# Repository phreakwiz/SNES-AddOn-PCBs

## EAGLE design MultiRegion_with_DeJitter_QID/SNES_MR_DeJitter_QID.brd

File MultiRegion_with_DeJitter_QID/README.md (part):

## Multi-Region Mod for any SNES

**Free your SNES**

(picture shows last prototype PCB installed on a SNS-CPU-RGB-01)

### Acknowledgement and Licensing

This PCB, its idea and design, is a confluence of multiple projects. All credits and rights are going to their respective creators:

- **SuperCIC-lock** by Ikari_01
  Copyright (c) 2010 by Maximilian Rehkopf under GNU GPLv2
  Source: [sd2snes homepage](https://sd2snes.de/blog/cool-stuff/supercic)
- **uIGR** by Ikari_01 and borti4938
  Copyright (c) 2010 by Maximilian Rehkopf under GNU GPLv2,
  and modifications copyright (c) 2015 by Peter Bartmann under GNU GPLv2
  Source: [sd2snes homepage](https://sd2snes.de/blog/cool-stuff/in-game-reset), [GitHub repository](https://github.com/borti4938/Switchless-Mods/tree/master/SNES/uigr_16f684)
- **Region Patch** built in SNES by Ikari_01 (initial idea and detection using SuperCIC-lock) and borti4938 (schematic refinement and CPLD implementation)
  Initial idea (c) 2012 ikari_01, CPLD implementation as used here covered in DeJitter license
  Source: [sd2snes homepage](https://sd2snes.de/files/supercic-213f.pdf)
- **DeJitter** by marqs85
  Copyright (c) 2017-2018 Markus Hiienkari under MIT
  and modifications and additions copyright (c) 2019 Peter Bartmann under MIT
  Source: [Original GitHub Repository](https://github.com/marqs85/snes_dejitter), [Forked GitHub repository](https://github.com/borti4938/snes_dejitter/tree/regionpatch%2Bdejitter)
- **DFO** by micro
  Copyright / created 2015 by Jakob Schäfer without licensing (but given to retro community)
  Source: mirror in [this repository](./dfo), with minor adaptations and with several original sources noted [in the Source.md file](./dfo/SOURCE.md)
- **PCB design** by borti4938
  Copyright (c) 2019 by Peter Bartmann under GNU GPLv3

### Features

- **SuperCIC:** lockout chip replacement 50Hz/60Hz switch cabability
- **uIGR:** controller input sniffing to perform certain actions like reset or 60Hz and 50Hz switch up on certain combinations
- **Region Patch:** overrides region protection based on picture processing status reads
- **DeJitter:** removes jitter on sync for NTSC mode
- **DFO:** dual frequency oscillator, here used to switch between base clocks for 50Hz, 60Hz video-modes

### PCB Description

#### Solder Pads

These are just general descriptions of the in- and outputs. Please refer to the installation instructions for each [specific mainboard version](./installation/) (if exists) for suitable connections.

- **/Rst.o:** (output (2x))
  Low-active reset output. This has to be connected with CIC-lock pad 10 / S-APU pin 100. Connect either pad.
- **Rst.i:** (input)
  High-active reset input. This pad has to be connected with the CIC-lock pad 8 (reset button).
- **LED.Re:** (output)
  LED driver for replacement LED; usually red. Output is active on 60Hz and auto video mode and off on 50Hz (or vice versa if SJ21 is set (common anode LED))
- **LED.Gr:** (output)
  LED driver for replacement LED; usually green. Output is active on 50Hz and auto video mode and off on 60Hz (or vice versa if SJ21 is set (common anode LED))
- **Ctrl.port.10:** (input)
  Input for controller 1 sniffing (data latch signal). _Port_ refers to flat cable connector of the whole controller panel, i.e. pin is equivalent for controller connector pin 3.
- **Ctrl.port.8:** (input)
  Input for controller 1 sniffing (data clock signal). _Port_ refers to flat cable connector of the whole controller panel, i.e. pin is equivalent for controller connector pin 2.
- **Ctrl.port.6:** (input)
  Input for controller 1 sniffing (serial data signal). _Port_ refers to flat cable connector of the whole controller panel, i.e. pin is equivalent for controller connector pin 4.
- **Vmode:** (output)
  Output sets the PPU video mode at S-PPU1 pin 24 and S-PPU2 pin 30 or at the S-CPUN pin 111. Output is active on 50Hz mode and inactive on 60Hz mode.
- **/Vmode:** (output (2x))
  Output sets the video encoding at the video encoder, which is pin 19 of the S-ENC and pin 9 of the S-RGB. Connect just on of the pads!
- **Clk.CIC:** (input)
  Input for the SuperCIC-lock clock, which comes from CIC pad 7.
- **MClk.o:** (output)
  Output for the (de-jittered) master clock of the SNES. This is approx. 21.477MHz in NTSC mode and appr. 17.734MHz (1Chip-SNES, SJ32 not set) or appr. 21.281MHz (non-1Chip, SJ32 set) in PAL mode. Please refer to the general installation note to see whether and how to connect this pad properly.
- **CClk.o:** (output)
  Output of the color carrier, which is appr. 3.380MHz in NTSC mode and appr. 4.433MHz in PAL mode. Please refer to the general installation note to see whether and how to connect this pad properly.
- **/CS.i:** (input (2x since SMR20190813)
  Input of the 'original' (non-de-jittered) composite sync. This comes from pin 100 S-PPU2 or pin 151 S-CPUN.
- **/CS.o buf:** (output)
  Buffered (de-jittered) composite sync output. This is meant to be connected directly to the multiout pin 3. Note: The PAL SNES has 12V connected to this pin, which has to be removed.
- **/CS.o raw:** (output (2x))
  Raw output of the CPLD, which has 3.3V high and 0V low level. Connect it to the video encode, which is pin 8 of the S-ENC or pin 7 of the S-RGB (both chips allows 2.0V for input high, so 3.3V high is sufficient.)

#### Jumper

- **SJ11:** alternative clock for the SuperCIC; close this jumper if you don't connect the _Clk.CIC_ pad in order to use the clock meant for the CIC-key
- **SJ21:** close this jumper if you use a LED with a common anode. Otherwise leave this jumper untouched
- **SJ31:** closing this jumper permanently disables the de-jitter function. This solder jumper is a bit larger to give the installer the option to connect a slide switch here (_speed-runner discussions_)
- **SJ32:** short this jumper if the board is installed in a non-1Chip-SNES (SNES Jr. / SNES2 are also 1Chip-SNES)
- **SJ61:** distributes clock output to cartridge slot pin 1. This jumper **must not** be closed in 1Chip-SNES. Side note: if SJ32 is open, SJ61 has to open, too.
- **SJ63:** (since SMR20200323) decides which color carrier is forwarded to output. This jumper has two option; you must not close both jumpers!
  - SJ63.1: (marked with a dot) outputs color carrier derived from non-dejittered clock.  
    Use this if you have a problem with discoloring on composite sync or S-Video ([issue thread at shmups](https://shmups.system11.org/viewtopic.php?p=1389666#p1389666))  
    Btw: this is default for all earlier version of the modding board flashed with the current firmware. If you need the other color carrier, just go back to a previous version.
  - SJ63.2: outputs color carrier derived from dejittered clock.  
    (I personally need to use this clock as my TV does not like the color carrier from non-dejittered clock)
  - Again: **You must not close both jumpers!**
- **SJ93**: (since SMR20200323) controls sync level of buffered csync output. Sync level:
  - opened: appr. 1.87V @ 75ohm termination i.e. needs a resistor inside the sync wire further attanuating the signal. Designed to work for cables with 470 ohm resistor inside resulting in appr. 450mV @ 75ohm termination
  - closed: appr. 300mV @ 75ohm termination suitable for pass through wired cables at sync, works with standard TV / scaler setup

#### Firmware

U1, U2, U3 and U5 need a firmware flashed to the chip. U1 and U2 have to be programmed prior to assembly whereas the PCB provides ICSP headers for the other ones.

- **U1:** PIC 16F630 microcontroller with - [SuperCIC-lock firmware](http://sd2snes.de/files/supercic.zip)
- **U2:** PIC 16F684 microcontroller with [uIGR firmware](https://raw.githubusercontent.com/borti4938/Switchless-Mods/master/SNES/uigr_16f684/snes_uigr_684_with_lock.hex)

Use a PICKit, TL866CS or similar programmer.

- **U3:** EPM7032 CPLD with clock switch, region patch and de-jitter firmware. You have to choose the right one depending on your modding board version.

  - [Version SMR20190813 (and later)](https://github.com/borti4938/snes_dejitter/blob/regionpatch+dejitter/output_files/multi_func/multi_function.pof?raw=true)
  - [Version SMR20190603 and earlier](https://github.com/borti4938/snes_dejitter/blob/regionpatch+dejitter/output_files/multi_func_legacy/multi_func_legacy.pof?raw=true)

Use an Altera USB Blaster (or clone) for flashing the firmware.

After assembly, the modding board has to be powered for flashing the firmware. This can be done by using the DFO programmer connected with V_target set to 5V (or 3.3V) if the modding board is not installed yet (other power solutions are possible, but please use the 5V power supply rail to not harm the DC converters. Or you can simply switch on the SNES for programming. Of course, the CPLD can be also flashed prior to assembly if you have a proper adapter at hand.

- **U5:** CDCE913 with [appropriate configuration](https://github.com/borti4938/SNES-AddOn-PCBs/blob/master/MultiRegion_with_DeJitter_QID/dfo/clockpro/snes_multi_region.hex?raw=true)

Use the DFO programmer to flash the PLL. The [DFO readme](./dfo/SOURCE.md) describes how to properly perform the flashing.

### Installation Notes

#### Manufacturing the PCB

You can choose any manufacturer which you prefer. All files for manufacturing including the design files are provided in subfolder [gerber/pcb/](./gerber/pcb/). As the PCB is designed in EAGLE (current version 7.4.2), gerbers are exported in the actual format. However, some services have problem while automatically analyze those like OSHPark or JCLPCB. Please try the older format in [gerber/pcb.eagle_legacy_export/](./gerber/pcb.eagle_legacy_export/).

For using the OSHPark service, you can also look for my [uploaded project](https://oshpark.com/profiles/borti4938). (check version)

**IMPORTANT**
Please use a substrate thickness of 0.8mm in order to make installation easier.

#### Assembly

##### Sourcing the Parts

For sourcing the parts, please be referred to the [Bill Of Materials](https://github.com/borti4938/SNES-AddOn-PCBs/blob/master/MultiRegion_with_DeJitter_QID/BOM.xlsx?raw=true)

##### Soldering

The PCB is designed with having hand soldering in mind. Most complicated footprints are probably the 44TQFP package of the CPLD or the 14TSSOP of the CDCE913.

However, if you plan to use a stencil, you can use the [stencil gerber file](./gerber/stencil/SNES_MR_DeJitter_QID.GTP). All SMDs are placed in top layer.

**IMPORTANT**
SuperCIC (PIC16F630-I/SL) and uIGR (PIC16F684-I/SL) need firmware flashed prior to soldering as mentioned later in this document.

#### Installation

This is not a complete installation manual. It's moreover a general overview on _'HowTo'_. Installation manuals are provided in the [subfolder installation](./installation/) once ready. I cannot test every single mainboard revision (there are too many out there), so the installation folder will grow from time to time once I see a proper report of an installation or I did an installation on a specific mainboard version on my own.

##### Preparation of SNES

###### General Steps

- remove original CIC-lock (or at least lift pins 1, 2, 10 and 11)
- remove LED from front panel (large SNES only)

###### Specific Steps for 1Chip-SNES

- lift pin 111 from S-CPUN
- remove X1
- lift pin 9 from S-RGB (or cut encoding mode jumper at bottom side of SNES mainboard (NTSC board revisions))

###### Specific Steps for Non-1Chip-SNES

- lift pin 24 of S-PPU1 and pin 30 of S-PPU2
- disconnect Master-Clock
  - SNSP-CPU-01/02: lift pin 4 of the S-CLK or remove R73 (0ohm jumper)
  - different methods for NTSC mainboards
- lift CSYNC input pin of the video encoder
  - pin 8 of S-ENC
  - pin 7 of S-RGB
- if you want to switch color carrier:
  - PAL: lift pin 5 of the S-CLK
  - NTSC: lift pin 3 of the S-PPU2
  - SNES with S-ENC: lift pin 19 (or cut encoding mode jumper at bottom side of SNES mainboard (NTSC board revisions))
  - SNES with S-RGB: lift pin 9 (or cut encoding mode jumper at bottom side of SNES mainboard (NTSC board revisions)) 

##### Installation of PCB

###### General Steps

- Solder PCB in place under the cartridge slot. Be aware of the orientation (pin marking must match)
- put the replacement dual LED where the original was (use a small piece of hot glue if needed)...  
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
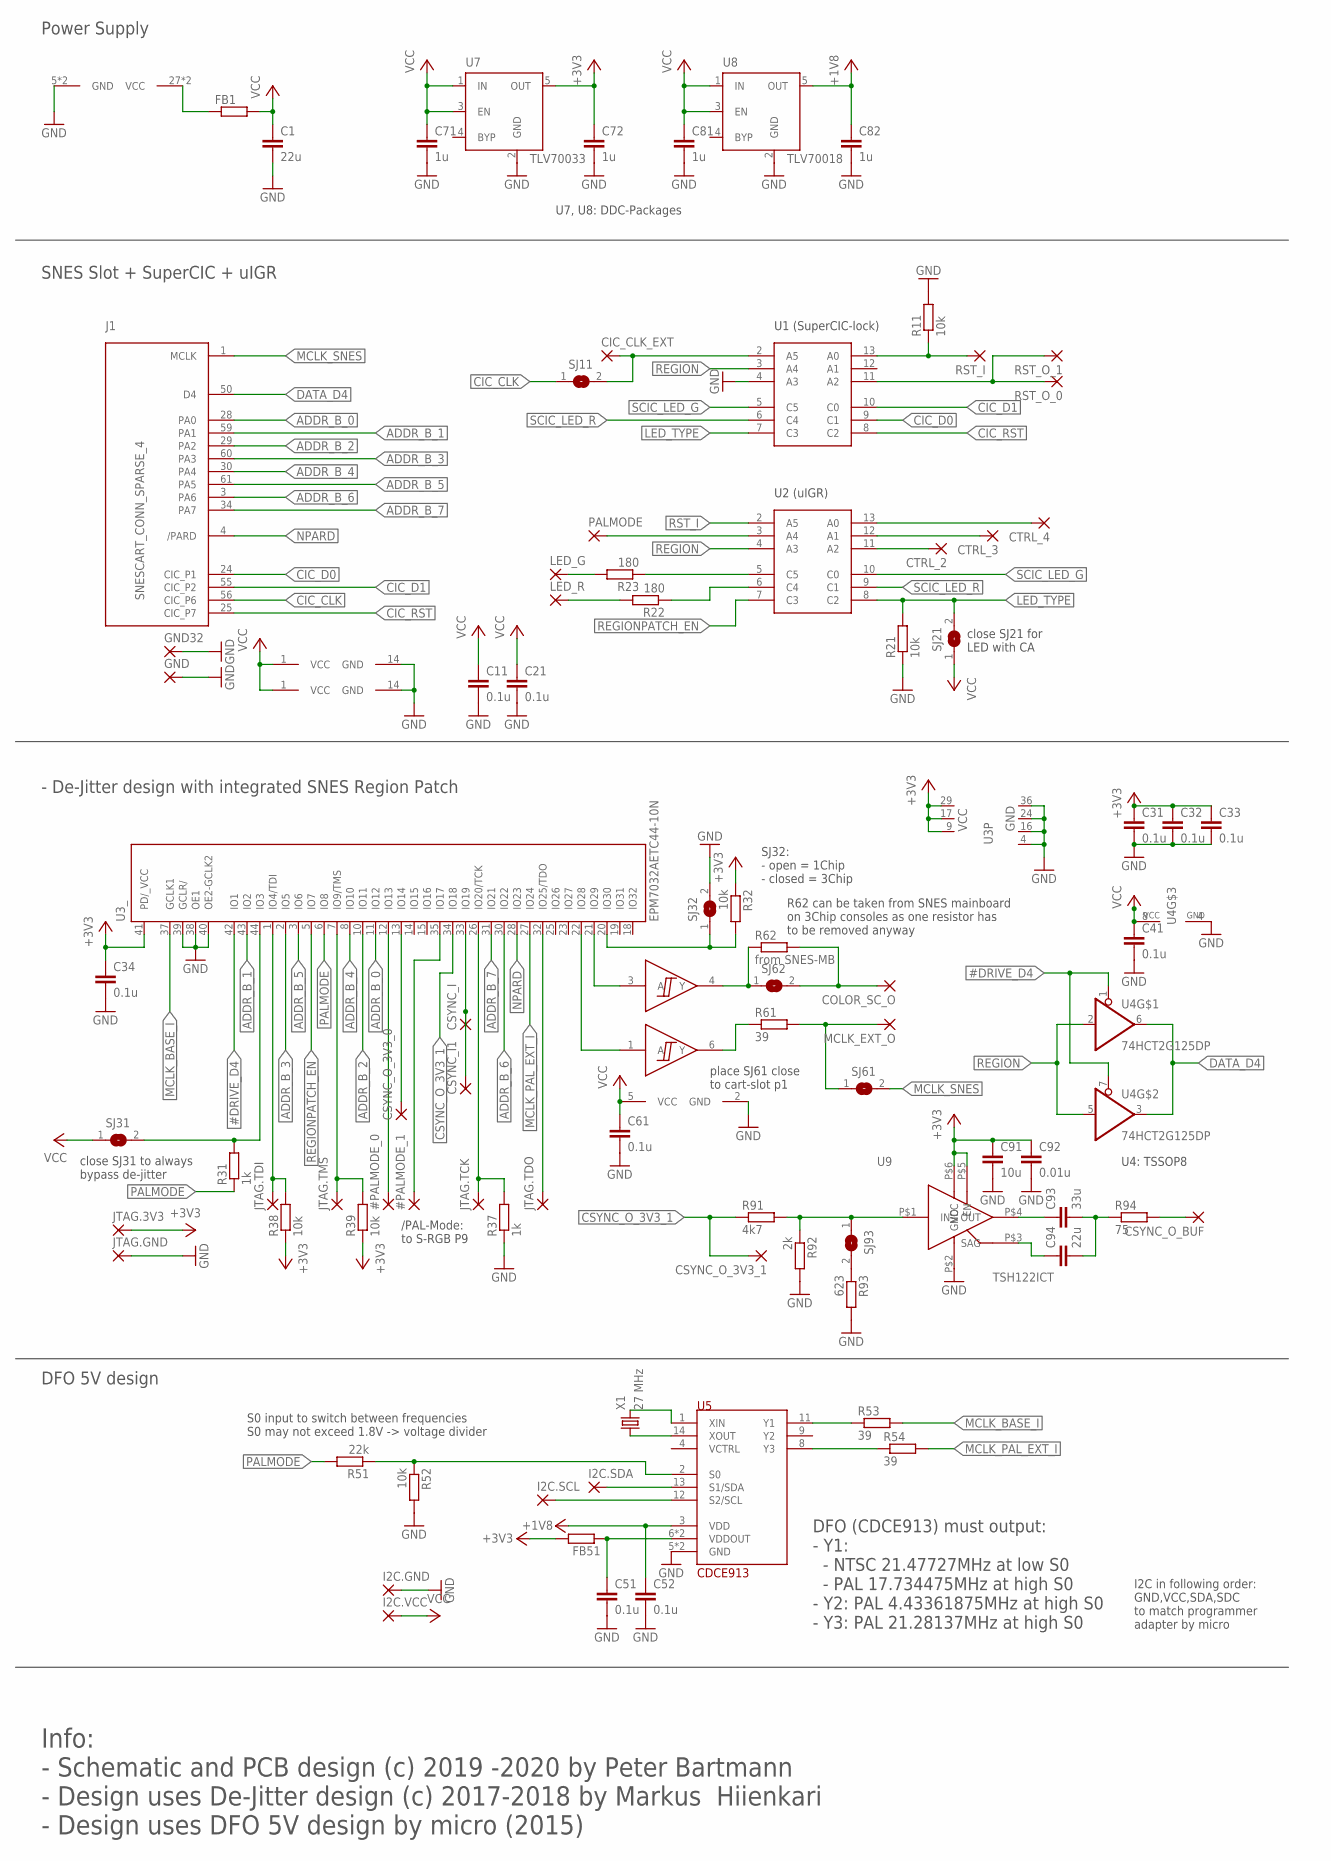
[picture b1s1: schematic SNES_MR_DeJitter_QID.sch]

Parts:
#PALMODE_0, #PALMODE_1: SMD2; SMD1,27-2,54
C1, C94: 22u; C0603
C11, C21, C31, C32, C33, C34, C41, C51, C52, C61: 0.1u; C0603
C71, C72, C81, C82: 1u; C0603
C91: 10u; C0603
C92: 0.01u; C0603
C93: 33u; C0805
CIC_CLK_EXT: SMD2; SMD1,27-2,54
COLOR_SC_O: SMD2; SMD1,27-2,54
CSYNC_I, CSYNC_I1: SMD2; SMD1,27-2,54
CSYNC_O_3V3_0, CSYNC_O_3V3_1: SMD2; SMD1,27-2,54
CSYNC_O_BUF: SMD2; SMD1,27-2,54
CTRL_2, CTRL_3, CTRL_4: SMD2; SMD1,27-2,54
FB1, FB51: R-EU_R0603; R0603
GND, GND32: SMD2; SMD1,27-2,54
I2C.GND, I2C.SCL, I2C.SDA, I2C.VCC: 1,6/0,8
J1: SNESCART_CONN_SPARSE_4
JTAG.3V3, JTAG.GND, JTAG.TCK, JTAG.TDI, JTAG.TDO, JTAG.TMS: 1,6/0,8
LED_G: SMD2; SMD1,27-2,54
LED_R: SMD2; SMD1,27-2,54
MCLK_EXT_O: SMD2; SMD1,27-2,54
PALMODE: SMD2; SMD1,27-2,54
R11, R21, R32, R38, R39, R52: 10k; R0603
R22, R23: 180; R0603
R31, R37: 1k; R0603
R51: 22k; R0603
R53, R54, R61: 39; R0603
R62: from SNES-MB; R0805
R91: 4k7; R0603
R92: 2k; R0603
R93: 623; R0603
R94: 75; R0603
RST_I: SMD2; SMD1,27-2,54
RST_O_0, RST_O_1: SMD2; SMD1,27-2,54
SJ11, SJ21, SJ32, SJ61, SJ62, SJ93: SJSMALL; SJ_SMALL
SJ31: SJ
U1: SuperCIC_lock; PIC16F630
U2: uIGR; PIC16F630
U3: EPM7032AETC44-10N; TQFP44
U4: 74HCT2G125DP; SSOP08
U5: CDCE913; TSSOP14
U6: 2G17TI_DBV; SOT-23-6
U7: TLV70033; SOT23-5
U8: TLV70018; SOT23-5
U9: TSH122ICT; SC70
X1: 27 MHz; HC49UP

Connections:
#DRIVE_D4: U3.42 (IO1), U4.1 (OE), U4.7 (OE)
+1V8: C52.1, C82.1, U5.3 (VDD), U8.5 (OUT)
+3V3: C31.1, C32.1, C33.1, C34.1, C72.1, C91.1, C92.1, FB51.2, JTAG.3V3.1, R32.1, R38.1, R39.1, U3.9 (VCC), U3.17 (VCC), U3.29 (VCC), U3.41 (PD/_VCC), U7.5 (OUT), U9.P$5 (EN), U9.P$6 (VCC)
+5V: C1.1, C11.1, C21.1, C41.1, C61.1, C71.1, C81.1, FB1.2, I2C.VCC.1, SJ21.1, SJ31.1, U1.1 (VCC), U2.1 (VCC), U4.8 (VCC), U6.5 (VCC), U7.1 (IN), U7.3 (EN), U8.1 (IN), U8.3 (EN)
+5V_SNES: FB1.1, J1.27 (VCC), J1.58 (VCC)
ADDR_B_0: J1.28 (PA0), U3.11 (IO12)
ADDR_B_1: J1.59 (PA1), U3.43 (IO2)
ADDR_B_2: J1.29 (PA2), U3.10 (IO11)
ADDR_B_3: J1.60 (PA3), U3.2 (IO5)
ADDR_B_4: J1.30 (PA4), U3.8 (IO10)
ADDR_B_5: J1.61 (PA5), U3.3 (IO6)
ADDR_B_6: J1.3 (PA6), U3.30 (IO22)
ADDR_B_7: J1.34 (PA7), U3.31 (IO21)
CIC_CLK: J1.56 (CIC_P6), SJ11.1
CIC_CLK_EXT: CIC_CLK_EXT.1, SJ11.2, U1.2 (A5)
CIC_D0: J1.24 (CIC_P1), U1.9 (C1)
CIC_D1: J1.55 (CIC_P2), U1.10 (C0)
CIC_RST: J1.25 (CIC_P7), U1.8 (C2)
COLOR_SC_O: COLOR_SC_O.1, R62.2, SJ62.2
COLOR_SC_O_PRE: R62.1, SJ62.1, U6.4 (Y)
COLOR_SC_PRE: U3.21 (IO29), U6.3 (A)
CSYNC_I: CSYNC_I.1, CSYNC_I1.1, U3.33 (IO19)
CSYNC_O: CSYNC_O_BUF.1, R94.2
CSYNC_O_3V3_0: CSYNC_O_3V3_0.1, U3.13 (IO14)
CSYNC_O_3V3_1: CSYNC_O_3V3_1.1, R91.1, U3.34 (IO18)
CTRL2: CTRL_2.1, U2.11 (A2)
CTRL3: CTRL_3.1, U2.12 (A1)
CTRL4: CTRL_4.1, U2.13 (A0)
DATA_D4: J1.50 (D4), U4.3 (O), U4.6 (O)
DEJITTER_BYPASS: R31.2, SJ31.2, U3.44 (IO3)
GND: C1.2, C11.2, C21.2, C31.2, C32.2, C33.2, C34.2, C41.2, C51.2, C52.2, C61.2, C71.2, C72.2, C81.2, C82.2, C91.2, C92.2, GND.1, GND32.1, I2C.GND.1, J1.5 (GND), J1.36 (GND), JTAG.GND.1, R11.2, R21.1, R37.1, R52.2, R92.2, R93.2, SJ32.2, U1.4 (A3), U1.14 (GND), U2.14 (GND), U3.4 (GND), U3.16 (GND), U3.24 (GND), U3.36 (GND), U3.38 (OE1), U3.39 (GCLR/), U3.40 (OE2-GCLK2), U4.4 (GND), U5.5 (GND), U5.10 (GND), U6.2 (GND), U7.2 (GND), U8.2 (GND), U9.P$2 (GND)
LED_G: LED_G.1, R23.2
LED_R: LED_R.1, R22.2
LED_TYPE: R21.2, SJ21.2, U1.7 (C3), U2.8 (C2)
MCLK_BASE_I: R53.2, U3.37 (GCLK1)
MCLK_BASE_I_PRE: R53.1, U5.11 (Y1)
MCLK_EXT_O: MCLK_EXT_O.1, R61.2, SJ61.1
MCLK_EXT_O_PRE: R61.1, U6.6 (Y)
MCLK_EXT_PRE: U3.22 (IO28), U6.1 (A)
MCLK_PAL_EXT_I: R54.2, U3.27 (IO24)
MCLK_PAL_EXT_I_PRE: R54.1, U5.8 (Y3)
MCLK_SNES: J1.1 (MCLK), SJ61.2
unnamed: R91.2, R92.1, SJ93.1, U9.P$1 (IN)
unnamed: U5.1 (XIN), X1.2
unnamed: U5.14 (XOUT), X1.1
unnamed: C94.1, U9.P$3 (SAG)
unnamed: C93.1, U9.P$4 (OUT)
unnamed: C93.2, C94.2, R94.1
unnamed: R93.1, SJ93.2
NPALMODE_0: #PALMODE_0.1, U3.12 (IO13)
NPALMODE_1: #PALMODE_1.1, U3.35 (IO17)
NPARD: J1.4 (/PARD), U3.28 (IO23)
PALMODE: PALMODE.1, R31.1, R51.2, U2.3 (A4), U3.6 (IO8)
PALMODE.1V8: R51.1, R52.1, U5.2 (S0)
REGION: U1.3 (A4), U2.4 (A3), U4.2 (I), U4.5 (I)
REGIONPATCH_EN: U2.7 (C3), U3.5 (IO7)
RST_I: R11.1, RST_I.1, U1.13 (A0), U2.2 (A5)
RST_O: RST_O_0.1, RST_O_1.1, U1.11 (A2)
SCIC_LED_G: U1.5 (C5), U2.10 (C0)
SCIC_LED_R: U1.6 (C4), U2.9 (C1)
SCL: I2C.SCL.1, U5.12 (S2/SCL)
SDA: I2C.SDA.1, U5.13 (S1/SDA)
SEL_SNES_1CHIP: R32.2, SJ32.1, U3.20 (IO30)
TCK: JTAG.TCK.1, R37.2, U3.26 (IO20/TCK)
TDI: JTAG.TDI.1, R38.2, U3.1 (IO4/TDI)
TDO: JTAG.TDO.1, U3.32 (IO25/TDO)
TMS: JTAG.TMS.1, R39.2, U3.7 (IO9/TMS)
UIGR_LED_G: R23.1, U2.5 (C5)
UIGR_LED_R: R22.1, U2.6 (C4)
VDDOUT: C51.1, FB51.1, U5.6 (VDDOUT), U5.7 (VDDOUT)

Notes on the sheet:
/PAL-Mode: to S-RGB P9
DFO (CDCE913) must output: - Y1: - NTSC 21.47727MHz at low S0 - PAL 17.734475MHz at high S0 - Y2: PAL 4.43361875MHz at high S0 - Y3: PAL 21.28137MHz at high S0
place SJ61 close to cart-slot p1
close SJ31 to always bypass de-jitter
close SJ21 for LED with CA
Info: - Schematic and PCB design (c) 2019 -2020 by Peter Bartmann - Design uses De-Jitter design (c) 2017-2018 by Markus Hiienkari - Design uses DFO 5V design by micro (2015)
S0 input to switch between frequencies S0 may not exceed 1.8V -> voltage divider
I2C in following order: GND,VCC,SDA,SDC to match programmer adapter by micro
U1 (SuperCIC-lock)
U2 (uIGR)
DFO 5V design
- De-Jitter design with integrated SNES Region Patch
SNES Slot + SuperCIC + uIGR
Power Supply
U7, U8: DDC-Packages
U4: TSSOP8
SJ32: - open = 1Chip - closed = 3Chip
R62 can be taken from SNES mainboard on 3Chip consoles as one resistor has to be removed anyway

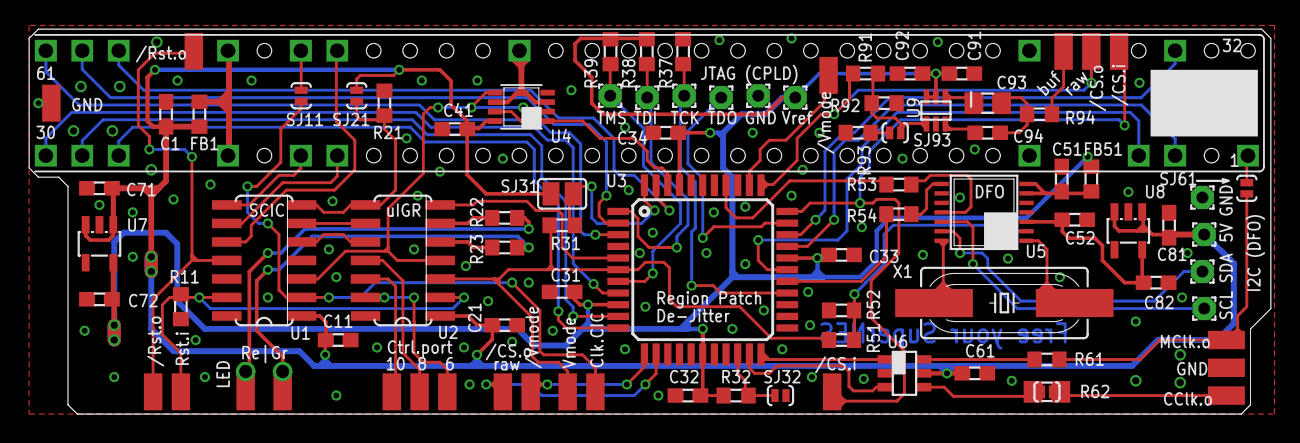
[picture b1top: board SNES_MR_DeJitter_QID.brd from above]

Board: 2 copper layers, 85.2 x 26.4 mm, 89 parts (0 on the bottom side), 70 nets.

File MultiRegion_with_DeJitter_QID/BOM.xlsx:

Version: | SMR20200323
Number of PCBs: |  |  | 3
Designator | MPN | QTY/PCB | QTY | DESCRIPTION | VALUE | PACKAGE | NOTES | Digikey | Mouser | Firmware
U1 | PIC16F630-I/SL | 1 | 3 | 8bit Microcontroller |  | SOIC-14 | needs SuperCIC-lock firmware preflashed |  |  | http://sd2snes.de/files/supercic.zip
U2 | PIC16F684-I/SL | 1 | 3 | 8bit Microcontroller |  | SOIC-14 | needs uIGR FW preflashed |  |  | https://github.com/borti4938/Switchless-Mods/tree/master/SNE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
U3 | EPM7032AETC44-10N | 1 | 3 | CPLD, 32MCs, 3.3Vcc, 5V tolerant I/Os |  | TQFP44 | fw can be flashed using JTAG header |  |  | https://github.com/borti4938/snes_dejitter/tree/regionpatch%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
U4 | 74HCT2G125DP | 1 | 3 | IC BUFFER NON-INVERT with /OE |  | TSSOP8, SOT505-2
U5 | CDCE913PWR | 1 | 3 | IC PROG PLL VCXO CLK SYN |  | 14TSSOP | I2C accessable over PCB header |  |  | https://github.com/borti4938/SNES-AddOn-PCBs/tree/master/Mul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
U6 | SN74LVC2G17DBVR | 1 | 3 | IC BUFFER NON-INVERT, Schmitt Trigger |  | SOT-23-6
U7 | TLV70033DDCR | 1 | 3 | LDO 3.3V |  | SOT-23-5
U8 | TLV70018DDCR | 1 | 3 | LDO 1.8V |  | SOT-23-5
U9 | TSH122ICT | 1 | 3 | Video Driver, 6dB, 1 Ch. |  | SC-70-6
X1 | 9C-27.000MAAJ-T | 1 | 3 | CRYSTAL 27.0000MHZ 18PF | 27MHz | HC-49/US
C1,C94 | (22uF cap 0603) | 2 | 6 | Ceramic capacitor, X5R | 22uF / 16V | SMD0603
C11,C21,C31,C32,C33,C34,C41,C51,C52,C61 | (100nF cap 0603) | 10 | 30 | Ceramic capacitor, X7R | 0.1uF / 50V | SMD0603
C71,C72,C81,C82 | (1uF cap 0603) | 4 | 12 | Ceramic capacitor, X5R | 1uF / 6.3V | SMD0603
C91 | (10uF cap 0603) | 1 | 3 | Ceramic capacitor, X5R | 10uF / 25V | SMD0603
C92 | (10nF cap 0603) | 1 | 3 | Ceramic capacitor, X7R | 0.01uF / 50V | SMD0603
C93 | (33uF cap 0805) | 1 | 3 | Ceramic capacitor, X5R | 33uF / 5V | SMD0805
FB1,FB51 | MPZ1608S221A | 2 | 6 | Ferrit bead, power line |  | SMD0603
R11,R21,R32,R38,R39,R52 | RC0603FR-0710KL | 6 | 18 | Resistor | 10k | SMD0603
R22,R23 | RC0603FR-07180RL | 2 | 6 | Resistor | 180 | SMD0603
R31,R37 | RC0603FR-071KL | 2 | 6 | Resistor | 1k | SMD0603
R51 | RC0603FR-0722KL | 1 | 3 | Resistor | 22k | SMD0603
R53,R54,R61 | RC0603FR-0739RL | 3 | 9 | Resistor | 39 | SMD0603
R62 |  | 0 | 0 | Resistor / Jumper |  | SMD0805 | resistor taken from SNES mainboard / jumper closed, if CClk.o directly connecte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
R91 | RC0603FR-074K7L | 1 | 3 | Resistor | 4.7k | SMD0603
R92 | RC0603FR-076K19L | 1 | 3 | Resistor | 6.19k | SMD0603
R93 | RC0603FR-07523RL | 1 | 3 | Resistor | 523 | SMD0603
R94 | RC0603FR-0775RL | 1 | 3 | Resistor | 75 | SMD0603
Optional components
(LED) | WP59SURKSGW | 1 | 3 | example replacement LED bi-color with common cathode | red / green
(pin header for LED connection) | 61900211021 | 1 | 3 | pin header for LED connection
 | 61900211621 | 1 | 3 | connector housing 2-pos. Female 2.54mm
 | 61900113722DEC | 2 | 6 | connector socket for 22-28AWG crimp

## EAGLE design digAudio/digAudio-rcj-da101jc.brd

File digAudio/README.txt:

Solder Joints:

A mapping Pads of PCB to S-DSP/S-APU is given on the bottoms silkscreen

-----------------------------------------------------------------------------------

Components:

See BOM.xlsx

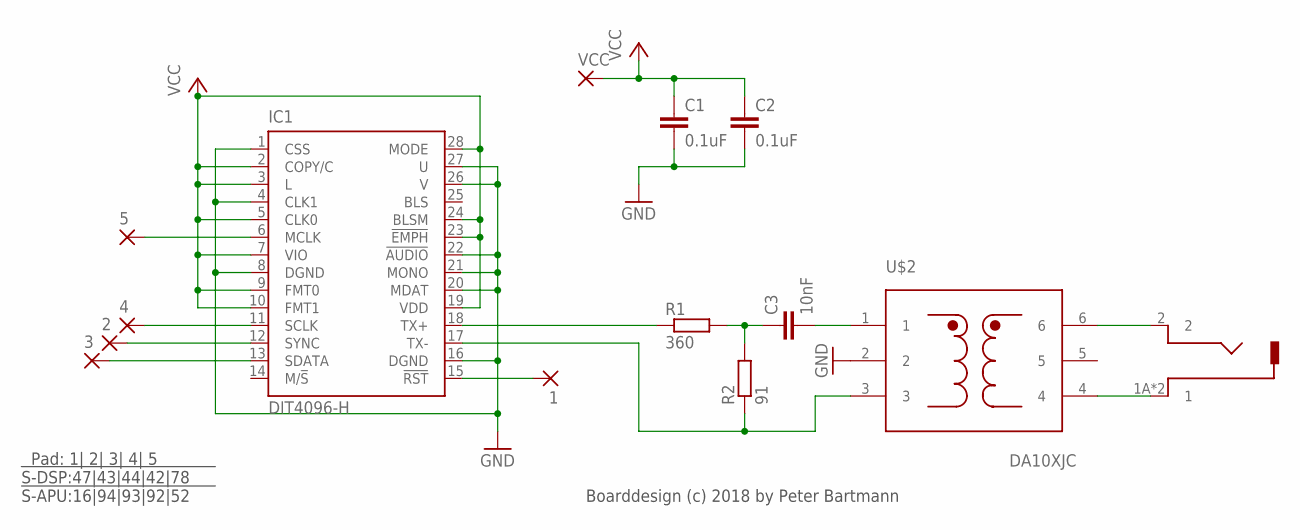
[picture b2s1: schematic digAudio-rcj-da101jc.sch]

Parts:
1, 2, 3, 4, 5: SMD1; SMD0,8-1,6
C1, C2: 0.1uF; C0603
C3: 10nF; C0603
IC1: DIT4096-H; PW_R-PDSO-G28
R1: 360; R0603
R2: 91; R0603
U$1: RCJ-013-SMT-TR; RCJ_01X_SMT_MODIFIED
U$2: DA10XJC; DA101JC
VCC: SMD2; SMD1,27-2,54

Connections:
GND: C1.2, C2.2, IC1.1 (CSS), IC1.4 (CLK1), IC1.8 (DGND), IC1.16 (DGND), IC1.20 (MDAT), IC1.21 (MONO), IC1.22 (!AUDIO), IC1.26 (V), IC1.27 (U), U$2.2
unnamed: IC1.18 (TX+), R1.1
unnamed: 1.P$1, IC1.15 (!RST)
unnamed: 2.P$1, IC1.12 (SYNC)
unnamed: 4.P$1, IC1.11 (SCLK)
unnamed: 3.P$1, IC1.13 (SDATA)
unnamed: 5.P$1, IC1.6 (MCLK)
unnamed: IC1.17 (TX-), R2.1, U$2.3
unnamed: C3.1, R1.2, R2.2
unnamed: U$1.2, U$2.6
unnamed: U$1.1A (1), U$1.1B (1), U$2.4
unnamed: C3.2, U$2.1
VCC: C1.1, C2.1, IC1.2 (COPY/C), IC1.3 (L), IC1.5 (CLK0), IC1.7 (VIO), IC1.9 (FMT0), IC1.10 (FMT1), IC1.19 (VDD), IC1.23 (!EMPH), IC1.24 (BLSM), IC1.28 (MODE), VCC.1

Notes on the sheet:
Pad: 1| 2| 3| 4| 5 S-DSP:47|43|44|42|78 S-APU:16|94|93|92|52
Boarddesign (c) 2018 by Peter Bartmann

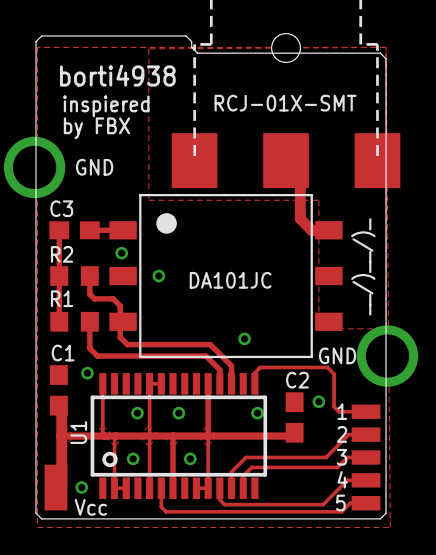
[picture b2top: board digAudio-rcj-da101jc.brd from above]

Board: 2 copper layers, 19.4 x 26.8 mm, 14 parts (0 on the bottom side), 13 nets.

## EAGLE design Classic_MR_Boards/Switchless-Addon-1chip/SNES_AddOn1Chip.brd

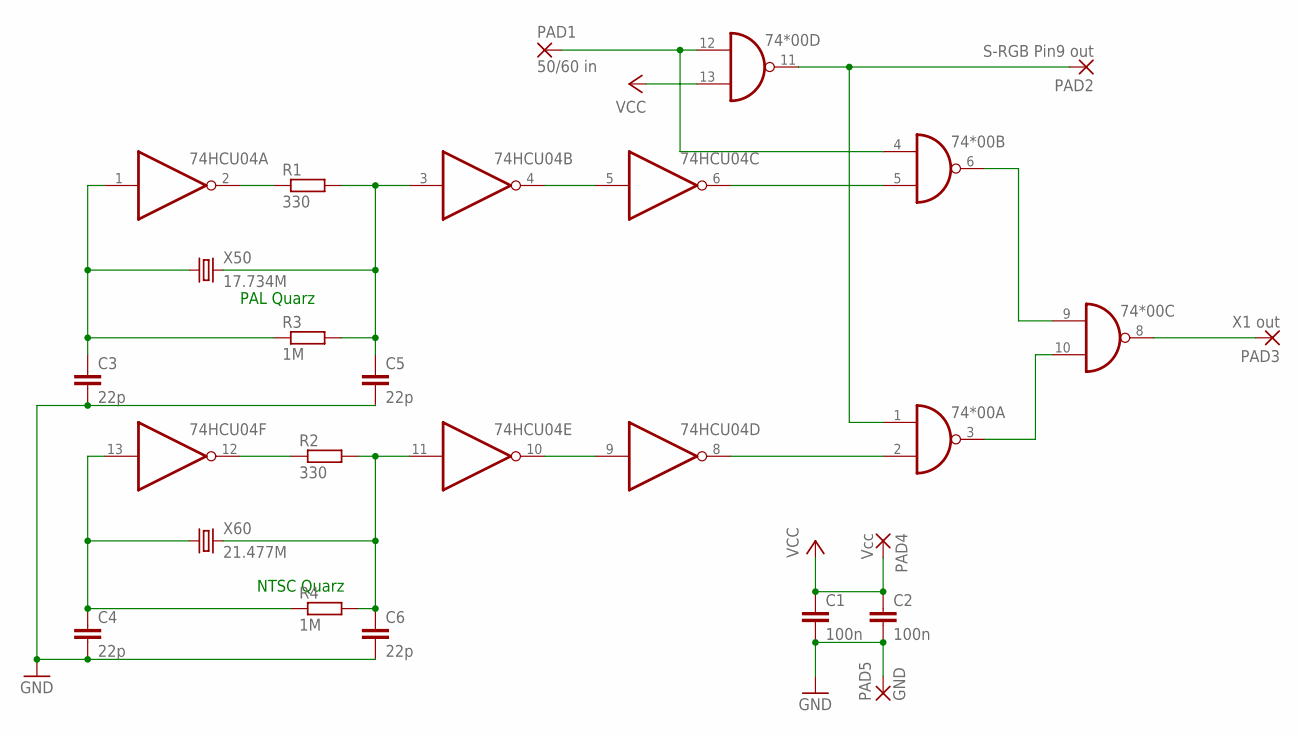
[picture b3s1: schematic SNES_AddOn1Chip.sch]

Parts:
74*00: 7400D; SO14
74HCU04: 74HC04D; SO14
C1, C2: 100n; Z0805
C3, C4, C5, C6: 22p; Z0805
PAD1: 50/60 in; SMD1,27-2,54
PAD2: S-RGB Pin9 out; SMD1,27-2,54
PAD3: X1 out; SMD1,27-2,54
PAD4: Vcc; SMD2,54-5,08
PAD5: GND; SMD2,54-5,08
R1, R2: 330; Z0805
R3, R4: 1M; Z0805
X50: 17.734M; MY_SMD_CRYSTAL2
X60: 21.477M; MY_SMD_CRYSTAL2

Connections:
GND: 74*00.7 (GND), 74HCU04.7 (GND), C1.2, C2.2, C3.2, C4.2, C5.2, C6.2, PAD5.1
unnamed: 74HCU04.1 (I), C3.1, R3.1, X50.1
unnamed: 74HCU04.3 (I), C5.1, R1.2, R3.2, X50.2
unnamed: 74HCU04.13 (I), C4.1, R4.1, X60.1
unnamed: 74HCU04.11 (I), C6.1, R2.2, R4.2, X60.2
unnamed: 74*00.3 (O), 74*00.10 (I1)
unnamed: 74*00.6 (O), 74*00.9 (I0)
unnamed: 74*00.4 (I0), 74*00.12 (I0), PAD1.1
unnamed: 74*00.1 (I0), 74*00.11 (O), PAD2.1
unnamed: 74*00.8 (O), PAD3.1
unnamed: 74HCU04.2 (O), R1.1
unnamed: 74HCU04.4 (O), 74HCU04.5 (I)
unnamed: 74*00.5 (I1), 74HCU04.6 (O)
unnamed: 74*00.2 (I1), 74HCU04.8 (O)
unnamed: 74HCU04.9 (I), 74HCU04.10 (O)
unnamed: 74HCU04.12 (O), R2.1
VCC: 74*00.13 (I1), 74*00.14 (VCC), 74HCU04.14 (VCC), C1.1, C2.1, PAD4.1

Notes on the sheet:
PAL Quarz
NTSC Quarz

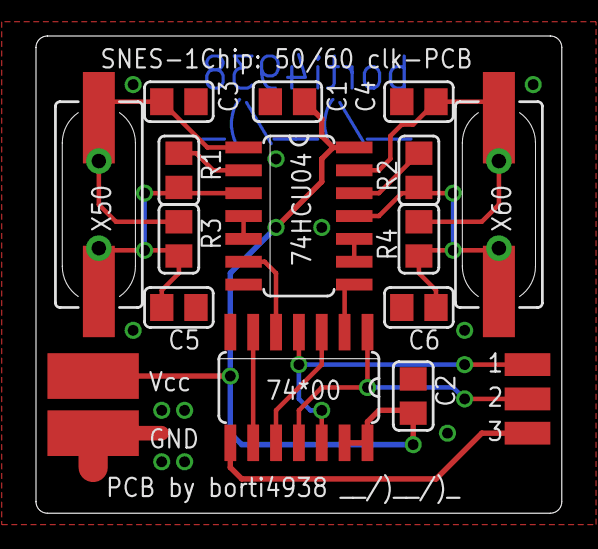
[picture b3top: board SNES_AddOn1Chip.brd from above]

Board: 2 copper layers, 29.2 x 26.5 mm, 19 parts (0 on the bottom side), 17 nets.

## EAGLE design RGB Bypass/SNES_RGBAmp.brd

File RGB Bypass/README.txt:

SNES_RGBAmp: for 1Chip-01/02 boards  
SNES_RGBAmp_1Chip03+: for 1Chip-03 boards and for SNES Mini/SFC Jr.  
  
-----------------------------------------------------------------------------------  
  
Solder Joints:  
  
  R - red image component from S-CPUN pin156  
  G - green image component from S-CPUN pin157  
  B - blue image component from S-CPUN pin158  
  /CS - composite sync from S-CPUN pin151  
  
Look for appropriate Vias and other equivalent solder joints ;)  
  
solder PCB directly beneath the MultiAV  
deactivate the RGB-output of S-RGB by lifting pin20, 22 and 24 from mainboard or simply by removing R15, R16 and R17 from the SNES mainboard (not SNES mini / SFC Jr.).  
  
equivalent installation guides: http://retrorgb.com/snes.html  
(with this version, there is no need to adjust any brightness issues ;)  
  
While modding some components on the PCB may vary depending on your RGB cable you want to use.  
See the notes related to the components!    
  
-----------------------------------------------------------------------------------  
  
Component needed:  
  
1. Common Parts:  
 - 1x THS7314 SOIC-8 package [board SNES_RGBAmp only]  
 - 1x THS7374 TSSOP-14 package [board SNES_RGBAmp_1Chip03+ only]  
  
 - 1x 22uF/6.3V tantalum capacitor type-C package  
 - 1x 100nF/50V ceramic capacitor 0805 package  
  
 - 2x 1.3kOhm resistor 0805 package (0.125W, 1% tolerance should be fine) [1]  
 - 2x 8.45kOhm resistor 0805 package (0.125W, 1% tolerance should be fine) [1]  
 - 1x 806Ohm resistor 0805 package (0.125W, 1% tolerance should be fine) [1]  
 - 1x 9.53kOhm resistor 0805 package (0.125W, 1% tolerance should be fine) [1]  
  
 - 1x 4.99kOhm resistor 0805 package (0.125W, 1% tolerance should be fine) [board SNES_RGBAmp_1Chip03+ only]  
 - 1x 4.30kOhm resistor 0805 package (0.125W, 1% tolerance should be fine) [board SNES_RGBAmp_1Chip03+ only]  
 - 1x 47pF/50V ceramic capacitor 0805 package [board SNES_RGBAmp_1Chip03+ only], [2]  
 - 3x 47pF/50V ceramic capacitor 0805 package [board SNES_RGBAmp_1Chip03+ in SNES Mini / SFC Jr. only], [2]  
  
 - 1x (between 75Ohm and 300Ohm [3]) resistor 0805 package (0.125W, 1% tolerance should be fine)  
 - 1x 330uF/6.3V tantalum capacitor type-D package  
  
2.a) Additional parts for using NTSC-cable schematic [4,5]:  
 - 3x 75Ohm resistor 0805 package (0.125W, 1% tolerance should be fine)  
  
2.b) Additional parts for using PAL-cable schematic [4,6]:  
 - 3x 39Ohm resistor 0805 package (0.125W, 1% tolerance should be fine)  
 - 3x 330uF/6.3V tantalum capacitor type-D package  
  
2.c) Additional parts for a cable with direct wiring RGB [4,5]:  
 - 3x 75Ohm resistor 0805 package (0.125W, 1% tolerance should be fine)  
 - 3x 330uF/6.3V tantalum capacitor type-D package  
  
-----------------------------------------------------------------------------------  
  
Notes  
  
[1]  
You may want to replace them with 3x 750Ohm (R4, R5, R6) and 3x 7.5kOhm (R7, R8, R9) resistors for simplicity. This gives a 'warmer' image.  
  
[2]  
These capacitors and not really needed, but they are present in 1Chip-01/02/03 consoles for de-bouncing the MultiAV jack while plugging in and out.  
  
[3]  
depending on your TV: 75Ohm matches impedance, 300Ohm matches standard for sync. Personally I use 75Ohm. My TV does not have any problems with all values between 75Ohm and 300Ohm!  
  
[4]  
Just pic one (!) and do not buy all parts. If you use NTSC-cable schematic you have to short the three jumpers on the PCB.  
  
[5]  
If you have a PAL system, you may replace R18 on the SNES mainboard with a 75Ohm resistor 0805 package (0.125W, 1% tolerance should be fine).  
  
[6]  
If you have a NTSC system, you may replace R18 on the SNES mainboard with a 39Ohm resistor 0805 package (0.125W, 1% tolerance should be fine).

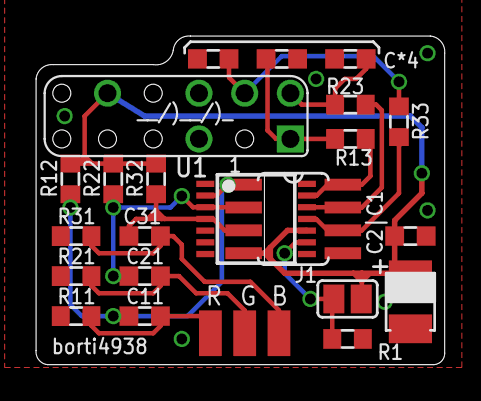
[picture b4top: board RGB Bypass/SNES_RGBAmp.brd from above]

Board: 2 copper layers, 22.7 x 18.3 mm, 25 parts (0 on the bottom side), 15 nets.

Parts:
B: SMD1,27-2,54
C1: 0.1u; C0603K
C2: 22u; SMC_B
C11, C21, C31: 82n; C0603K
C14, C24, C34: 47p; C0603K
G: SMD1,27-2,54
J1: SJ
R: SMD1,27-2,54
R1: 10k; R0603
R11, R13, R21, R23, R31, R33: R0603
R12, R22, R32: 3M6; R0603
U1: THS7374
U$1: SNES_MULTIAV_RGB_ONLY
U$2: THS7314

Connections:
GND: C1.2, C2.-, C14.2, C24.2, C34.2, R1.2, R11.1, R21.1, R31.1, U1.1, U1.5, U1.6, U$1.P$5, U$1.P$6, U$2.5
unnamed: C11.2, R12.1, U1.2, U$2.1
unnamed: C21.2, R22.1, U1.3, U$2.2
unnamed: J1.2, R1.1, U1.9
unnamed: R23.2, U1.12, U$2.7
unnamed: C14.1, R13.1, U$1.P$1
unnamed: C24.1, R23.1, U$1.P$2
unnamed: R13.2, U1.13, U$2.8
unnamed: R33.2, U1.11, U$2.6
unnamed: C34.1, R33.1, U$1.P$4
unnamed: C11.1, R.1, R11.2
unnamed: C21.1, G.1, R21.2
unnamed: B.1, C31.1, R31.2
R9: C31.2, R32.1, U1.4, U$2.3
VCC: C1.1, C2.+, J1.1, R12.2, R22.2, R32.2, U1.10, U$1.P$10, U$2.4

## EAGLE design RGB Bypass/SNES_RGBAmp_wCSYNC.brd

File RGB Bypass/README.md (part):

# The RGB Bypass Modding Boards for the SNES

There are three versions of the modding board available. Each version differs a bit in its components according to its purpose.

Take a look into the BOM, where the components are listed. Each modding board has its own page. Take also a look into the notes provided there to ensure that you create your board according to your needs.

#### Need a PCB?
Look at OSHPark: [SNES\_RGBAmp](https://oshpark.com/shared_projects/FGz6MoI9), [SNES\_RGBAmp\_wCSYNC](https://oshpark.com/shared_projects/hMAav8Ju), [SNES\_RGBAmp\_wCSYNC\_SVid](https://oshpark.com/shared_projects/QUsZvq5m)
  
Or use any other PCB service you like :) Make sure that your PCB will be produced on a **substrate of 0.8mm or thinner** to make installation smooth and easy.

If you want to go with [PCBWay.com](http://www.pcbway.com/) (non-affiliate link), you can also use [my affiliate link](http://www.pcbway.com/setinvite.aspx?inviteid=10658) to support me. Only do that if you want that!

Thank you very much!

# Installation Notes

## 1Chip-SNES (classical big model and SNES2 (Mini/Jr.))

PCB-Version to use:  

- SNES\_RGBAmp
  * mainly for 1Chip-01/02 boards
- SNES\_RGBAmp\_wCSYNC
  * mainly for 1Chip-03 boards and for SNES Mini/SFC Jr.
  * can be used in a 1Chip-01/02 if and only if the pin 3 of the MultiAV is freed (initially CSYNC (TTL) on NTSC and 12V on PAL models)
- SNES\_RGBAmp\_wCSYNC\_SVid **[1]**
  * same as SNES\_RGBAmp\_wCSYNC just with footprints for S-Video completion in SNES2 models (Mini/Jr.)

**Note [1]**  
Do not use this board in a classical big model SNES.

### Installation

#### Preparation of the SNES Mainboard

In the big model you have to free pin 1, 2 and 4 from the MultiAV, which are the outputs of the red, green and blue component, respectively. To do so, simply

- remove R15, R16 and R17 from the SNES mainboard

In the SNES2, these pins are unused, i.e., you don't have to do anything here.

If you want to /CSYNC from the modding board you also have to ensure that pin 3 of the MultiAV is also free. In a 1Chip-03 (NTSC only) and in SNES2 models, this is the case by default. In 1Chip-01/02 boards you have to:

- NTSC systems:
  * remove R12
  * optionally also remove R9 - R11 and Q1
- PAL systems:
  * remove R28 and D1

#### Decoupling caps at the MultiAV

There are some 47pF ceramic capacitors at the MultiAV at pin 1 - 4, namely C44 (pin 1), C45 (pin 2), C46 (pin 3) and C47 (pin 4). 
There are also some footprints for 47pF ceramic capacitors on the modding board , namely C14, C24, C34 and C44.  
Make sure that you either have for each pin at the MultiAV just a single cap installed. **If you unsure, just left the footprints on the MultiAV free as these caps are optional.**

**To sum up:**

- **1Chip-01/02** versions have all capacitors C44-C47 on board. So left C14-C44 on the modding board unpopulated.
- **1Chip-03** versions does not have C46 installed. So you can put C44 onto the modding board. C44 is directly next to R43.
- **SNES2** version do not C44-C47. This version even does not have footprints for them. So assemble C14-C44 on the modding board.

#### Board installation

Solder the modding board into your SNES directly on to of the MultiAV pins.  
Make sure that you don't have (electrical) contact between SNES mainboard and your modding board. If you are unsure, simply use isolating tape.  
The modding board has to face the long side of the SNES mainboard (opposite of output direction of the MultiAV port) with the solder pads.  

Connect the solder pads as follows:

- R - red image component from S-CPUN pin156
- G - green image component from S-CPUN pin157
- B - blue image component from S-CPUN pin158
- /CS - composite sync from S-CPUN pin151 (SNES\_RGBAmp\_wCSYNC and SNES\_RGBAmp\_wCSYNC\_SVid only)
- Y - luma component from S-RGB pin17 (SNES\_RGBAmp\_wCSYNC\_SVid only)
- C - chroma component from S-RGB pin12 (SNES\_RGBAmp\_wCSYNC\_SVid)
  
Look for appropriate vias and other equivalent solder joints ;) 

You find equivalent installation guide with pictures on [RetroRGB.com](http://retrorgb.com/snes.html)
(These guides do not exploit the decoupling caps. Just C46 is mentioned for /CSYNC in 1Chip-01/02 systems, but in a wrong way.)

### Misc
  
#### Jumper J1 - Low Pass Filter of the THS7373 and THS7374   

Both ICs are supported. The THS7373 has one SD-video low pass filter (used for /CSYNC) and three HD-video filters (used for R, G and B). The THS7374 has four SD-video filters.  
At the THS7373 the HD-video LPFs can be bypassed and at the THS7374 all four SD-video filters can be bypassed (using J1).  
  
The Jumper 1 is for bypassing the internal low pass filters.
 
- leave J1 open: internal filters are NOT bypassed  
- close J1: internal filters are bypassed (not effective for the SD-video channel of the THS7373)   
  
It is not possible to set the three HD-video (THS7373) or four SD-video (THS7374) low pass filters individually!

Normally, you don't need a LPF inside your SNES output. There are just a few capture cards out there who don't have a anti aliasing filter for is ADC inputs. There you have to have the LPF turned on.

On analog devices a LPF is not needed. On professional upscaling solutions like the Framemeister and OSSC you have an anti aliasing filter prior to its ADC circuits. This means you can turn the filter of the THS7374 off.

#### Some words on TTL or 75ohm /CSYNC

Actually I was under the impression that there are modern devices out there who need TTL sync. But that's not the case - at least I'm 99% sure. For example:

- OSSC needs 75ohm csync
- Framemeister needs 75ohm csync
- All consumer TVs needs 75ohm csync

Just a month ago I realised the reason, why most people want to requests TTL csync. Just because most csync cables have a resistor in the csync wire. And on the other hand - just a few weeks after that some YouTube videos arise and show how to modify RGB cables.  
A resistor inside the cable drops down the voltage level of /CSYNC to make it compatible to 75ohm inputs

Actually, all my consoles outputs true 75ohm csync (not approximately as others do "use a resistor of something in between..."), i.e. /CSYNC has negative impulses from 0V downto -300mV.  
And I went fine with it. I can run my OSSC without any problems, a Framemeister I borrowed a few weeks ago, went run fine, too :)
I even don't have to use sync filtering... 

#### Brightness and Ghosting Issues 

##### Brightness

The S-CPUN overdrives the outputs of R, G and B. This has the effect that R', G' and B' (signals going to your TV set) have higher peak-to-peak voltage values than the standard defines. In simple word, the **brightness is to high**.

The reduce the the brightness a common choice is to increase the load on the R, G and B lines (wires coming out of the S-CPUN) to correct that. Measurements were taken [by Ultron](http://assemblergames.com/l/threads/snes-mini-rgb-measurements.53053/). Thanks for that btw.
RetroRGB summarizes the final solution:

- for the 'regular' 1Chip model: [using 750 Ohm resistors](http://retrorgb.com/snes1chip.html)
- for the SNES Mini/Jr.: [using 1.2k Ohm resistors](http://retrorgb.com/snesminipremade7314.html)

The resistors, which are soldered to the SNES mainboard, got a place on the modding PCB (R11, R21 and R31). You may want to the SMD 0603 footprints for the resistors correcting the brightness, here.

**Alternatively**, you can adapt R3 on the SNES mainboard. This is a 1.6k Ohm resistor in SMD0805 (big model) or SMD0603 (SNES2) size.
From my measurements, replacing this resistor

- by a **1.74k Ohm** resistor in a big model SNES, and
- by a **1.69k Ohm** resistor in a SNES2 (Mini/Jr.)  
  (Just an estiamtion, I hadn't had a SNES2 for measurements here, so far)

seems to be a good choice. **By replacing R3 on the SNES mainboard** you must not use the brightness correction resistors R11, R21 and R31 on the modding board.

##### Ghosting

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
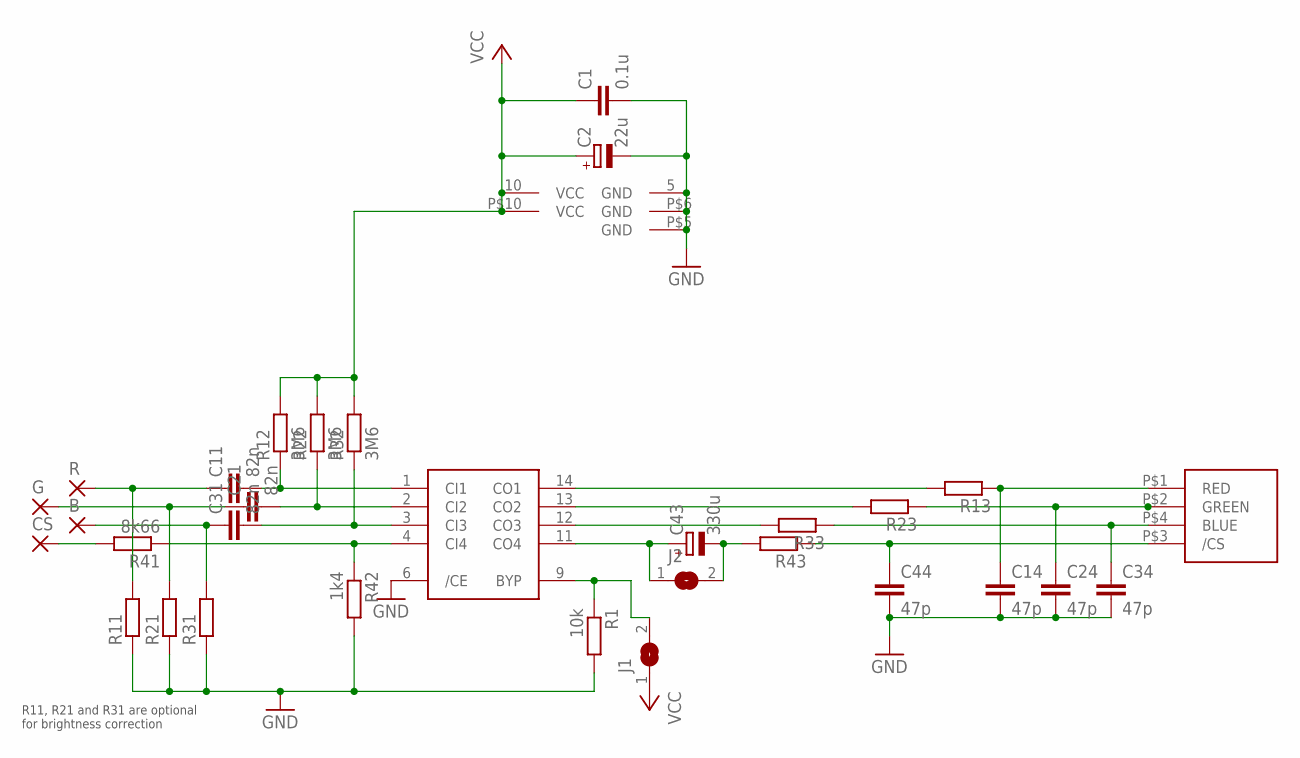
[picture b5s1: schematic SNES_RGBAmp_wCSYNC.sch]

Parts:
B: SMD2; SMD1,27-2,54
C1: 0.1u; C0603K
C2: 22u; SMC_B
C11, C21, C31: 82n; C0603K
C14, C24, C34, C44: 47p; C0603K
C43: 330u; SMC_D
CS: SMD2; SMD1,27-2,54
G: SMD2; SMD1,27-2,54
J1, J2: SJ
J3: SNES_MULTIAV_RGBC_ONLY
R: SMD2; SMD1,27-2,54
R1: 10k; R0603
R11, R13, R21, R23, R31, R33, R43: R-EU_R0603; R0603
R12, R22, R32: 3M6; R0603
R41: 8k66; R0603
R42: 1k4; R0603
U1: THS7374

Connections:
GND: C1.2, C2.-, C14.2, C24.2, C34.2, C44.2, J3.P$5 (GND), J3.P$6 (GND), R1.2, R11.1, R21.1, R31.1, R42.2, U1.5 (GND), U1.6 (/CE)
unnamed: C11.2, R12.1, U1.1 (CI1)
unnamed: C21.2, R22.1, U1.2 (CI2)
unnamed: J1.2, R1.1, U1.9 (BYP)
unnamed: C14.1, J3.P$1 (RED), R13.1
unnamed: C24.1, J3.P$2 (GREEN), R23.1
unnamed: R33.2, U1.12 (CO3)
unnamed: C34.1, J3.P$4 (BLUE), R33.1
unnamed: R41.1, R42.1, U1.4 (CI4)
unnamed: R13.2, U1.14 (CO1)
unnamed: R23.2, U1.13 (CO2)
unnamed: C11.1, R.1, R11.2
unnamed: C21.1, G.1, R21.2
unnamed: B.1, C31.1, R31.2
unnamed: CS.1, R41.2
unnamed: C43.+, J2.1, U1.11 (CO4)
unnamed: C43.-, J2.2, R43.2
unnamed: C44.1, J3.P$3 (/CS), R43.1
R9: C31.2, R32.1, U1.3 (CI3)
VCC: C1.1, C2.+, J1.1, J3.P$10 (VCC), R12.2, R22.2, R32.2, U1.10 (VCC)

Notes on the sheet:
R11, R21 and R31 are optional for brightness correction

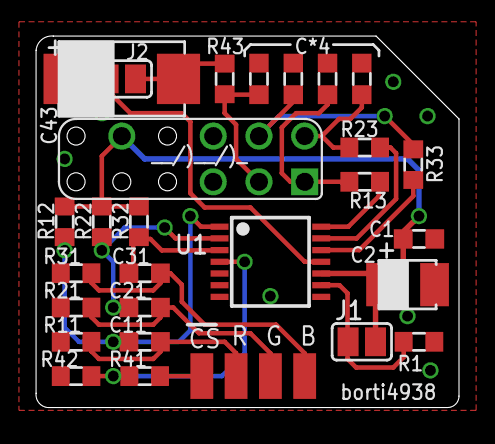
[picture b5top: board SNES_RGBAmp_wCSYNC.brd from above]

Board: 2 copper layers, 23.5 x 20.6 mm, 31 parts (0 on the bottom side), 20 nets.

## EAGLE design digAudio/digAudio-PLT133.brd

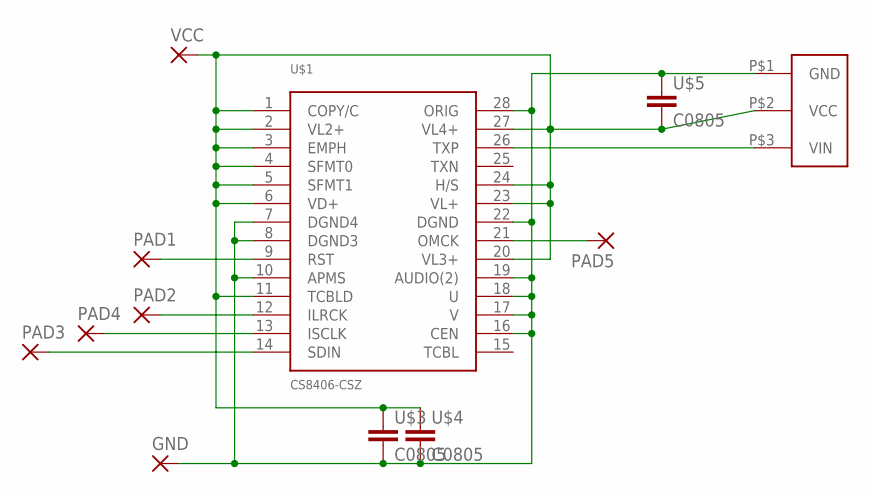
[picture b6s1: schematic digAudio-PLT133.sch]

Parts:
GND: SMD2; SMD1,27-2,54
PAD1, PAD2, PAD3, PAD4, PAD5: SMD2; SMD1,27-2,54
U$1: CS8406-CSZ; SO28W
U$3, U$4, U$5: C0805; Z0805
U$6: PLT133/T10W
VCC: SMD2; SMD1,27-2,54

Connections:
GND: GND.1, U$1.7 (DGND4), U$1.8 (DGND3), U$1.10 (APMS), U$1.16 (CEN), U$1.17 (V), U$1.18 (U), U$1.19 (AUDIO(2)), U$1.22 (DGND), U$1.28 (ORIG), U$3.2, U$4.2, U$5.1, U$6.P$1 (GND)
unnamed: U$1.26 (TXP), U$6.P$3 (VIN)
unnamed: PAD1.1, U$1.9 (RST)
unnamed: PAD2.1, U$1.12 (ILRCK)
unnamed: PAD4.1, U$1.13 (ISCLK)
unnamed: PAD3.1, U$1.14 (SDIN)
unnamed: PAD5.1, U$1.21 (OMCK)
VCC: U$1.1 (COPY/C), U$1.2 (VL2+), U$1.3 (EMPH), U$1.4 (SFMT0), U$1.5 (SFMT1), U$1.6 (VD+), U$1.11 (TCBLD), U$1.20 (VL3+), U$1.23 (VL+), U$1.24 (H/S), U$1.27 (VL4+), U$3.1, U$4.1, U$5.2, U$6.P$2 (VCC), VCC.1

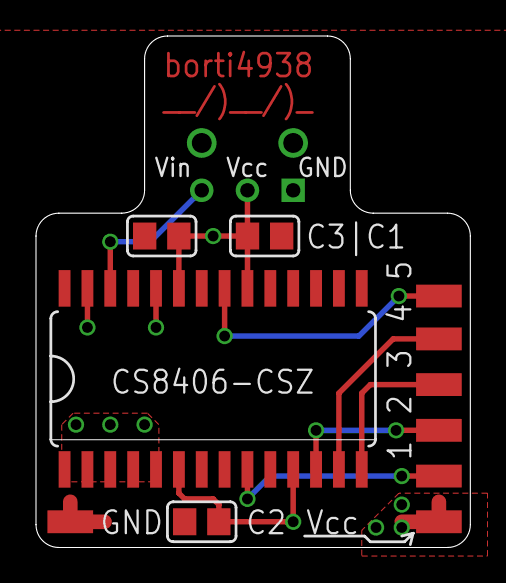
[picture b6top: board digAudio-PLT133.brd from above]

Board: 2 copper layers, 24.1 x 28.4 mm, 12 parts (1 on the bottom side), 8 nets.

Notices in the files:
parts and their libraries:
SparkFun: Licensing: CC v3.0 Share-Alike You are welcome to use this library for commercial purposes.
